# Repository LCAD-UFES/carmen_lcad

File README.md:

# carmen_lcad

Version of the Carmen Robot Navigation Toolkit developed by LCAD for IARA - the Intelligent Autonomous Robotic Autonomobile.

This software is being developed with the support of DI/LCAD/UFES and is financed in part by Fundação de Amparo à Pesquisa do Espírito Santo – Brazil (FAPES), Conselho Nacional de Desenvolvimento Científico e Tecnológico – Brasil (CNPq), and Coordenação de Aperfeiçoamento de Pessoal de Nível Superior – Brasil (CAPES).

## Instalação

### ➡️ Ubuntu 26.04 LTS — [**tutorial completo, aqui no repositório**](doc/migracao_ubuntu26/install/INSTALL_UBUNTU_26.04.md)

Esta é a versão recomendada e o tutorial mais atual. Ele fica **dentro do próprio
repositório** (não na wiki).

Resumo do caminho (o passo a passo com todos os detalhes está no tutorial):

```bash
git clone https://github.com/LCAD-UFES/carmen_lcad.git ~/carmen_lcad
# 1. adicionar o bloco #CARMEN no ~/.bashrc  (CARMEN_HOME, PATH, LD_LIBRARY_PATH)
# 2. instalar os pacotes apt  (build tools, Boost, OpenCV/PCL/g2o, GTK & cia.)
# 3. instalar o GtkGLExt da fonte, se ainda não estiver na máquina
cd $CARMEN_HOME/src
./configure --nojava --nocuda --noqt3       # Enter em todas as perguntas
make -j$(nproc)
```

Junto do tutorial estão os outros documentos da migração para o 26.04 — úteis quando
algo não compila:

| Documento | Para quê |
|---|---|
| [`install/INSTALL_UBUNTU_26.04.md`](doc/migracao_ubuntu26/install/INSTALL_UBUNTU_26.04.md) | **O tutorial de instalação.** Comece por aqui |
| [`install/00_` a `05_`](doc/migracao_ubuntu26/install/) | O detalhe e o porquê de cada passo do tutorial |
| [`CHANGELOG.md`](doc/migracao_ubuntu26/CHANGELOG.md) | Cada alteração de código/Makefile feita na migração, e por quê |
| [`AUDIT_DEPENDENCIAS.md`](doc/migracao_ubuntu26/AUDIT_DEPENDENCIAS.md) | Nome e versão de cada dependência no 26.04: o que mudou de nome, o que sumiu do apt |
| [`install/05_pendencias_conhecidas.md`](doc/migracao_ubuntu26/install/05_pendencias_conhecidas.md) | O que ficou pendente e por quê |

### Versões anteriores (wiki)

Português:

- [Install for Ubuntu 12.04](http://www.lcad.inf.ufes.br/wiki/index.php/Instala%C3%A7%C3%A3o_Carmen_para_Ubuntu_12.04.3)
- [Install for Ubuntu 16.04](https://github.com/LCAD-UFES/carmen_lcad/wiki/Installing-Carmen-LCAD-on-Ubuntu-16.04-(Portuguese))
- [Install for Ubuntu 18.04](https://github.com/LCAD-UFES/carmen_lcad/wiki/Installing-Carmen-LCAD-on-Ubuntu-18.04-(Portuguese))
- [Install for Ubuntu 20.04](https://github.com/LCAD-UFES/carmen_lcad/wiki/Installing-Carmen-on-Ubuntu-20.04-(Portuguese))

English:

- [Install for Ubuntu 12.04](https://github.com/LCAD-UFES/carmen_lcad/wiki/Installing-Carmen-LCAD-on-Ubuntu-12.04.3-(English))
- [Install for Ubuntu 14.04](https://github.com/LCAD-UFES/carmen_lcad/wiki/Installing-Carmen-LCAD-on-Ubuntu-14.04-(English))
- [Install for Ubuntu 16.04](https://github.com/LCAD-UFES/carmen_lcad/wiki/Installing-Carmen-LCAD-on-Ubuntu-16.04-(English))
- [Install for Ubuntu 18.04](https://github.com/LCAD-UFES/carmen_lcad/wiki/Installing-Carmen-LCAD-on-Ubuntu-18.04-(English))
- [Install for Ubuntu 20.04](https://github.com/LCAD-UFES/carmen_lcad/wiki/Installing-Carmen-on-Ubuntu-20.04-(English))

## Rodando

Os `.ini` de parâmetros ficam em `src/`, e os binários rodam a partir de `bin/` — os
caminhos dentro dos `.ini` são relativos a `bin/`.

```bash
cd $CARMEN_HOME/bin
./central
```

```bash
cd $CARMEN_HOME/bin
./proccontrol process-volta_da_ufes_playback_viewer_3D.ini
```

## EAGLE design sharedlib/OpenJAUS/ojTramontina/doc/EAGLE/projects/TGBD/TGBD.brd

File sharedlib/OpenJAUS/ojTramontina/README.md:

# ojEcoTech4
e.coTech4 Driver

Para rodar o sistema de freio ou volante, levante o barramento can (precisa do CANable):

 sudo ip link set can0 up type can bitrate 500000

Depois rode em terminais separados:

 ../ojNodeManager/bin/ojNodeManager ../ojNodeManager/nodeManager_EcoTech4.conf a
 ../ojTorc/bin/ojTorc {tecle w para entrar em Wrench Efforts Mode}
 bin/ojEcoTech4-2 can0 can0

Para compilar o codigo do ESP32:
 cd breaks
 . $HOME/esp/esp-idf/export.sh {o ponto eh importante}
 make
 make flash {para programar o ESP32}
 make monitor {para visualisar a saida do ESP32 via a sua USB}

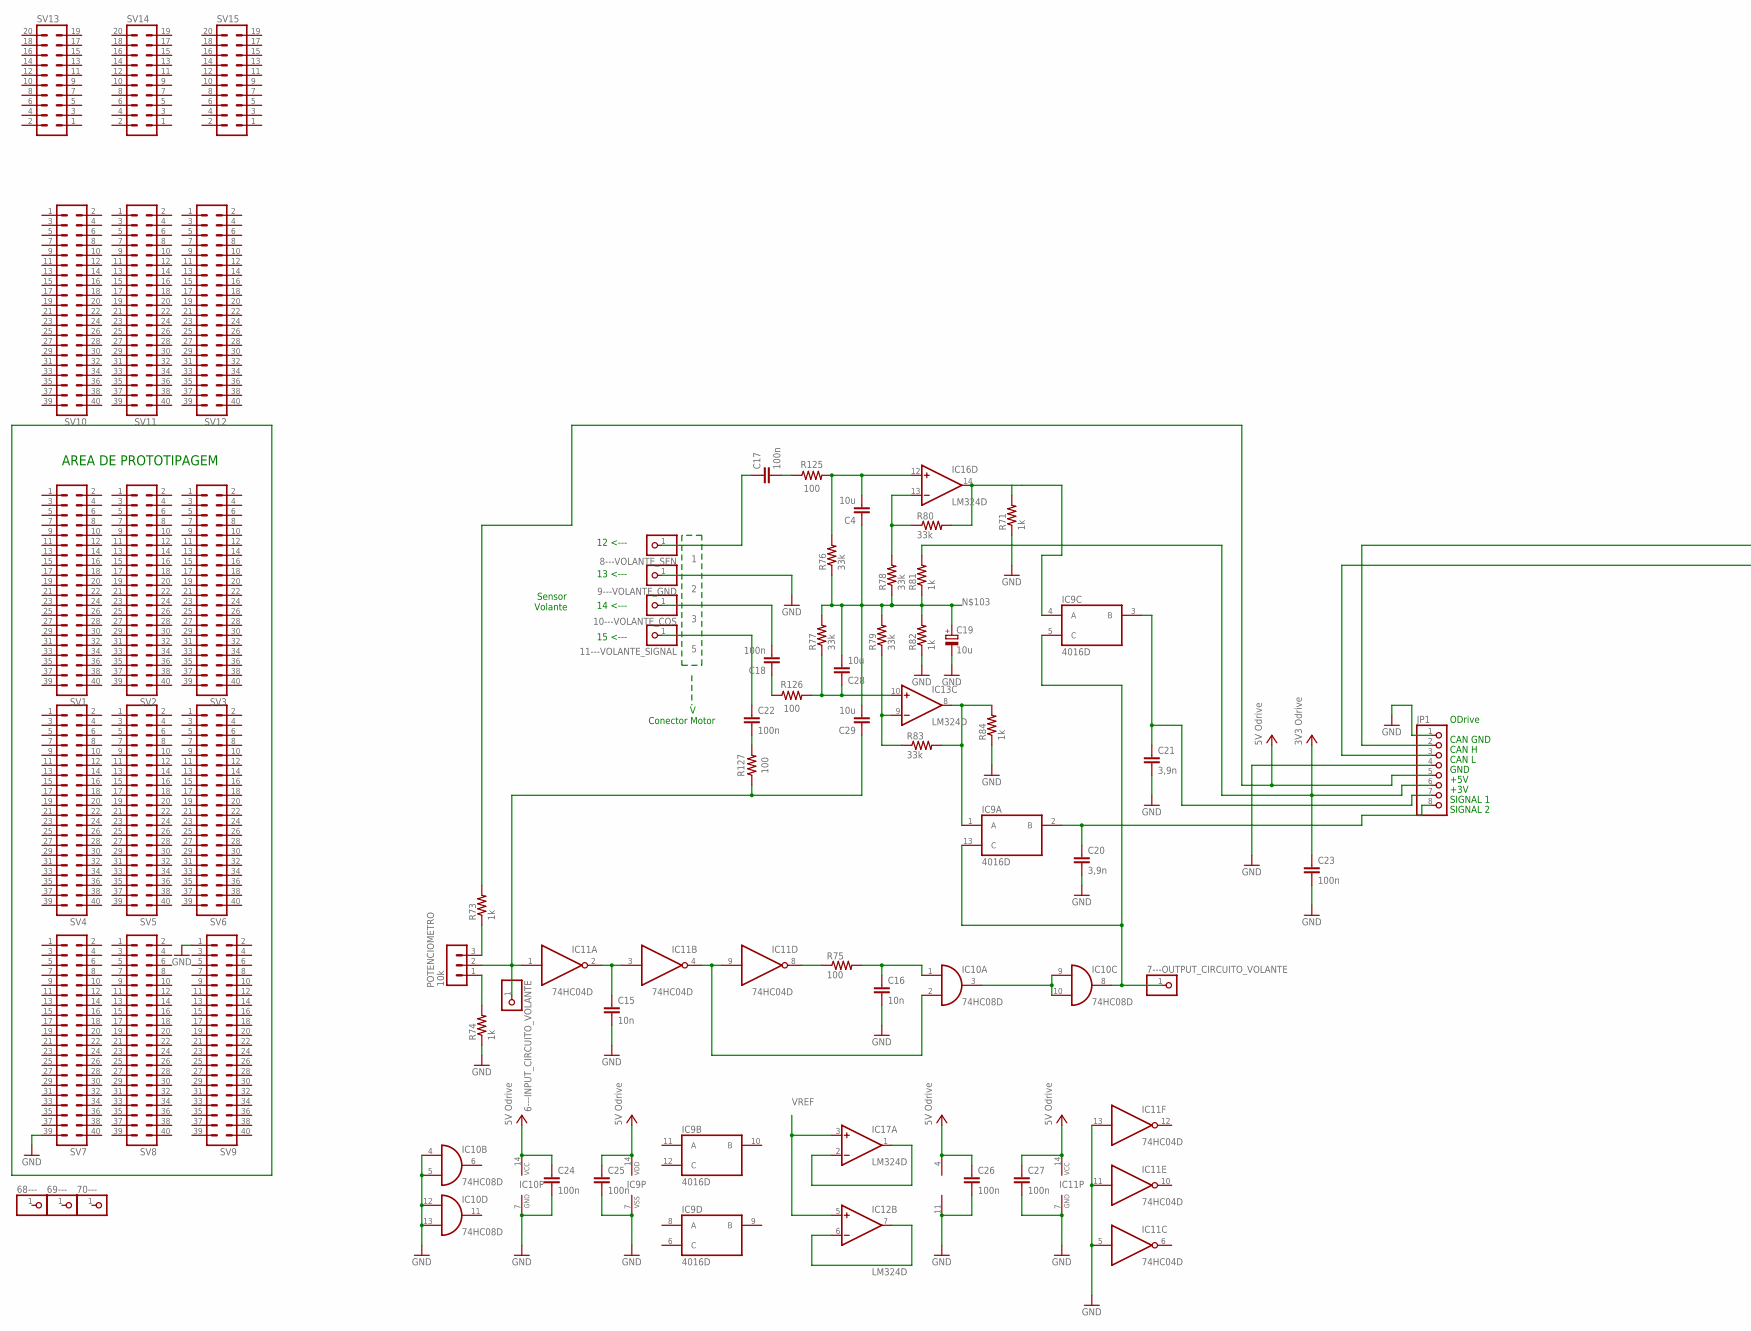
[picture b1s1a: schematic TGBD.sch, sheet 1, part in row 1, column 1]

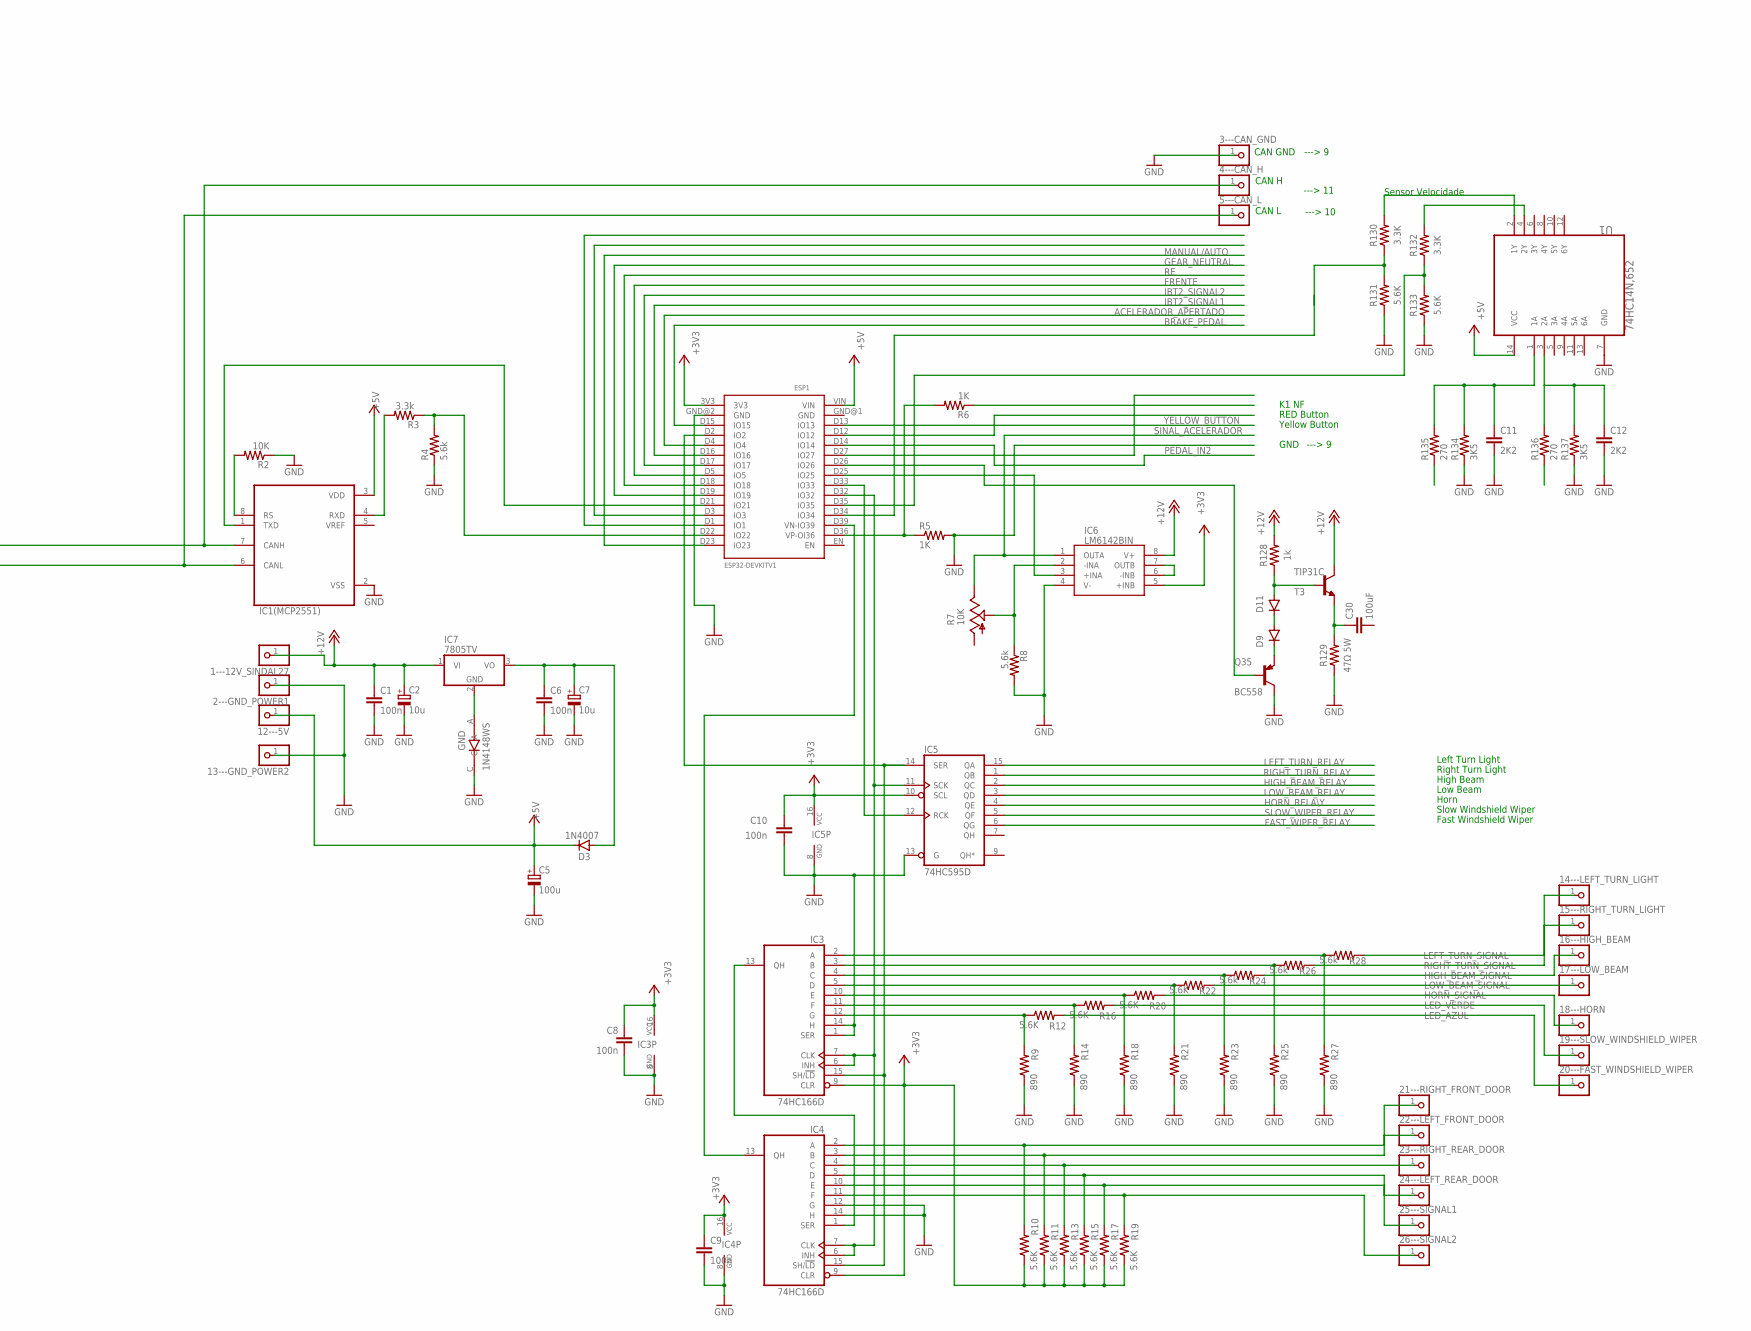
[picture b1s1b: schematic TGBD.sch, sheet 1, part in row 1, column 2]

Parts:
1---12V_SINDAL27, 2---GND_POWER1, 3---CAN_GND, 4---CAN_H, 5---CAN_L, 6---INPUT_CIRCUITO_VOLANTE, 7---OUTPUT_CIRCUITO_VOLANTE, 12---5V, 13---GND_POWER2, 14---LEFT_TURN_LIGHT, 15---RIGHT_TURN_LIGHT, 16---HIGH_BEAM, 17---LOW_BEAM, 18---HORN, 19---SLOW_WINDSHIELD_WIPER, 20---FAST_WINDSHIELD_WIPER, 21---RIGHT_FRONT_DOOR, 22---LEFT_FRONT_DOOR, 23---RIGHT_REAR_DOOR, 24---LEFT_REAR_DOOR, 25---SIGNAL1, 26---SIGNAL2, 68---, 69---, 70---: PINHD-1X1; 1X01
8---VOLANTE_SEN: 1; 1X01
9---VOLANTE_GND: 2; 1X01
10---VOLANTE_COS: 3; 1X01
11---VOLANTE_SIGNAL: 5; 1X01
C1, C6, C8, C9, C10, C17, C18, C22, C23, C24, C25, C26, C27: 100n; C0402
C2, C7, C19: 10u; A/3216-18R
C4, C28, C29: 10u; C0402
C5: 100u; UD-6,3X7,7_NICHICON
C11, C12: 2K2; C2.5-3
C15, C16: 10n; C0402
C20, C21: 3,9n; C0402
C30: 100uF; C2.5-2
D3: 1N4007; SOD123
D9, D11: 1N4148DO35-7; DO35-7
ESP1: ESP32DEVKITV1; ESP32-DEVKITV1
GND: 1N4148WS; SODFL2512X100N
IC1(MCP2551): MCP2551-I/SN; SOIC127P599X175-8N
IC3, IC4: 74HC166D; SO16
IC5: 74HC595D; SO16
IC6: LM6142BIN; DIP254P762X508-8
IC7: 7805TV; TO220V
IC8, IC12, IC13, IC16, IC17: LM324D; SO14
IC9: 4016D; SO14
IC10: 74HC08D; SO14
IC11: 74HC04D; SO14
JP1: PINHD-1X8; 1X08
POTENCIOMETRO: 10k; MA03-1
Q35: BC558; TO92260P520H933-3
R2: 10K; R0603
R3: 3.3k; R0402
R4, R8, R24, R26, R28: 5.6k; R0603
R5, R6: 1K; R0402
R7: 10K; CT6
R9, R14, R18, R21, R23, R25, R27: 890; R0603
R10, R11, R12, R13, R15, R16, R17, R19, R20, R22: 5.6K; R0603
R71, R73, R74, R81, R82, R84: 1k; R0402
R75: 100; R0603
R76, R77, R78, R79, R80, R83: 33k; R0402
R125, R126, R127: 100; RESC1005X40
R128: 1k; RESAD724W46L381D178B
R129: 47Ω 5W; RESAD724W46L381D178B
R130, R132: 3.3K; RESAD724W46L381D178B
R131, R133: 5.6K; RESAD724W46L381D178B
R134, R137: 3K5; 0204/7
R135, R136: 270; 0204/7
SV1, SV2, SV3, SV4, SV5, SV6, SV7, SV8, SV9, SV10, SV11, SV12: MA20-2
SV13, SV14, SV15: MA10-2
T3: TIP31C; TO220
U1: 74HC14N,652; DIP254P762X420-14

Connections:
3V3_ODRIVE: C23.1, JP1.6, R81.2
5V_ODRIVE: C24.1, C25.1, C26.1, C27.1, IC8.4 (V+), IC9.14 (VDD), IC10.14 (VCC), IC11.14 (VCC), JP1.5, R73.2
9---GND: 9---VOLANTE_GND.1
+3V3: C8.1, C9.1, C10.1, ESP1.3V3, IC3.9 (CLR), IC3.16 (VCC), IC4.9 (CLR), IC4.16 (VCC), IC5.10 (SCL), IC5.16 (VCC), IC6.5 (+INB), R10.1, R11.1, R13.1, R15.1, R17.1, R19.1
+5V: 12---5V.1, C5.+, D3.C, ESP1.VIN, IC1(MCP2551).3 (VDD), U1.14 (VCC); also elsewhere on the board
+12V: 1---12V_SINDAL27.1, C1.1, C2.+, IC6.8 (V+), IC7.1 (VI), R128.2, T3.2 (C); also elsewhere on the board
ACELERADOR_APERTADO: ESP1.D4 (IO4); also elsewhere on the board
AUTONOMO/NAO: ESP1.D27 (IO27)
BRAKE_PEDAL: ESP1.D15 (IO15)
FAST_WIPER_RELAY: IC5.6 (QG); also elsewhere on the board
FRENTE: ESP1.D5 (IO5); also elsewhere on the board
GEAR_NEUTRAL: ESP1.D19 (IO19)
GND: 2---GND_POWER1.1, 3---CAN_GND.1, 13---GND_POWER2.1, C1.2, C2.-, C5.-, C6.2, C7.-, C8.2, C9.2, C10.2, C11.2, C12.2, C15.2, C16.2, C19.-, C20.2, C21.2, C23.2, C24.2, C25.2, C26.2, C27.2, ESP1.GND@2 (GND), GND.C, IC1(MCP2551).2 (VSS), IC3.1 (SER), IC3.8 (GND), IC3.14 (H), IC4.8 (GND), IC4.12 (G), IC4.14 (H), IC5.8 (GND), IC5.13 (G), IC6.4 (V-), IC8.11 (V-), IC9.7 (VSS), IC10.4 (I0), IC10.5 (I1), IC10.7 (GND), IC10.12 (I0), IC10.13 (I1), IC11.5 (I), IC11.7 (GND), IC11.11 (I), IC11.13 (I), JP1.1, JP1.4, Q35.1 (C), R2.1, R4.1, R5.2, R8.2, R9.1, R14.1, R18.1, R21.1, R23.1, R25.1, R27.1, R71.1, R74.1, R82.1, R84.1, R129.1, R131.1, R133.1, R134.1, R137.1, SV7.39, SV9.1, U1.7 (GND); also elsewhere on the board
HIGH_BEAM_RELAY: IC5.2 (QC); also elsewhere on the board
HIGH_BEAM_SIGNAL: 16---HIGH_BEAM.1, R24.2; also elsewhere on the board
HORN_RELA\Y: IC5.4 (QE)
HORN_SIGNAL: 18---HORN.1, R20.2; also elsewhere on the board
IBT2_SIGNAL1: ESP1.D16 (IO16)
IBT2_SIGNAL2: ESP1.D17 (IO17)
LED_AZUL: 20---FAST_WINDSHIELD_WIPER.1, R12.2; also elsewhere on the board
LED_VERDE: 19---SLOW_WINDSHIELD_WIPER.1, R16.2; also elsewhere on the board
LEFT_TURN_RELAY: IC5.15 (QA); also elsewhere on the board
LEFT_TURN_SIGNAL: 14---LEFT_TURN_LIGHT.1, R28.2; also elsewhere on the board
LOW_BEAM_RELAY: IC5.3 (QD); also elsewhere on the board
LOW_BEAM_SIGNAL: 17---LOW_BEAM.1, R22.2; also elsewhere on the board
MANUAL/AUTO: ESP1.D23 (IO23); also elsewhere on the board
unnamed: IC6.6 (-INB), IC6.7 (OUTB)
unnamed: ESP1.D25 (IO25), IC6.3 (+INA)
unnamed: IC6.2 (-INA), R7.S, R8.1
unnamed: ESP1.D21 (IO21), IC1(MCP2551).1 (TXD)
unnamed: IC1(MCP2551).8 (RS), R2.2
unnamed: IC1(MCP2551).4 (RXD), R3.2
unnamed: 4---CAN_H.1, IC1(MCP2551).7 (CANH), JP1.2
unnamed: GND.A, IC7.2 (GND)
unnamed: ESP1.D32 (IO32), IC3.6 (INH), IC3.7 (CLK), IC4.6 (INH), IC4.7 (CLK), IC5.11 (SCK)
unnamed: ESP1.D22 (IO22), R3.1, R4.2
unnamed: C6.1, C7.+, D3.A, IC7.3 (VO)
unnamed: POTENCIOMETRO.3, R73.1
unnamed: ESP1.D36 (VP-OI36), R5.1, R6.2
unnamed: D9.C, Q35.3 (E)
unnamed: IC3.2 (A), R27.2, R28.1
unnamed: ESP1.D33 (IO33), IC5.12 (RCK)
unnamed: IC3.3 (B), R25.2, R26.1
unnamed: IC3.4 (C), R23.2, R24.1
unnamed: IC3.5 (D), R21.2, R22.1
unnamed: ESP1.D39 (VN-IO39), IC4.13 (QH)
unnamed: 21---RIGHT_FRONT_DOOR.1, IC4.2 (A), R10.2
unnamed: 22---LEFT_FRONT_DOOR.1, IC4.3 (B), R11.2
unnamed: 23---RIGHT_REAR_DOOR.1, IC4.4 (C), R13.2
unnamed: 24---LEFT_REAR_DOOR.1, IC4.5 (D), R15.2
unnamed: IC3.13 (QH), IC4.1 (SER)
unnamed: IC3.10 (E), R18.2, R20.1
unnamed: IC3.11 (F), R14.2, R16.1
unnamed: IC3.12 (G), R9.2, R12.1
unnamed: C15.1, IC11.2 (O), IC11.3 (I)
unnamed: IC10.3 (O), IC10.9 (I0), IC10.10 (I1)
unnamed: 5---CAN_L.1, IC1(MCP2551).6 (CANL), JP1.3
unnamed: POTENCIOMETRO.1, R74.2
unnamed: C4.1, C19.+, C28.2, C29.2, R76.1, R77.2, R78.1, R79.2, R81.1, R82.2
unnamed: IC11.8 (O), R75.1
unnamed: C16.1, IC10.1 (I0), R75.2
unnamed: IC10.2 (I1), IC11.4 (O), IC11.9 (I)
unnamed: C4.2, IC16.12 (+IN), R76.2, R125.2
unnamed: 8---VOLANTE_SEN.1, C17.1
unnamed: C11.1, R134.2, R135.2, U1.1 (1A)
unnamed: IC13.9 (-IN), R79.1, R83.1
unnamed: IC16.13 (-IN), R78.2, R80.1
unnamed: 10---VOLANTE_COS.1, C18.2
unnamed: IC9.1 (A), IC13.8 (OUT), R83.2, R84.2
unnamed: C20.1, IC9.2 (B), JP1.8
unnamed: IC17.1 (OUT), IC17.2 (-IN)
unnamed: IC12.6 (-IN), IC12.7 (OUT)
unnamed: 7---OUTPUT_CIRCUITO_VOLANTE.1, IC9.5 (C), IC9.13 (C), IC10.8 (O)
unnamed: C21.1, IC9.3 (B), JP1.7
unnamed: 11---VOLANTE_SIGNAL.1, C22.1
unnamed: C28.1, IC13.10 (+IN), R77.1, R126.2
unnamed: IC9.4 (A), IC16.14 (OUT), R71.2, R80.2
unnamed: 25---SIGNAL1.1, IC4.10 (E), R17.2
unnamed: 26---SIGNAL2.1, IC4.11 (F), R19.2
unnamed: C17.2, R125.1
unnamed: C18.1, R126.1
unnamed: C22.2, R127.2
unnamed: ESP1.D2 (IO2), IC3.15 (SH/!LD), IC4.15 (SH/!LD), IC5.14 (SER)
unnamed: ESP1.D26 (IO26), Q35.2 (B)
unnamed: D9.A, D11.C
unnamed: D11.A, R128.1, T3.1 (B)
unnamed: R130.1, R131.2
unnamed: R130.2, U1.2 (1Y)
unnamed: C30.1, R129.2, T3.3 (E)
unnamed: C12.1, R136.2, R137.2, U1.3 (2A)
unnamed: R132.2, U1.4 (2Y)
unnamed: ESP1.D35 (IO35), R132.1, R133.2
PEDAL_IN1: ESP1.D34 (IO34)
PEDAL_IN2: ESP1.D14 (IO14)
RE: ESP1.D18 (IO18); also elsewhere on the board
RIGHT_TURN_RELAY: IC5.1 (QB); also elsewhere on the board
RIGHT_TURN_SIGNAL: 15---RIGHT_TURN_LIGHT.1, R26.2; also elsewhere on the board
SINAL_ACELERADOR: IC6.1 (OUTA), R7.E; also elsewhere on the board
SLOW_WIPER_RELAY: IC5.5 (QF); also elsewhere on the board
V+: IC12.4 (V+), IC13.4 (V+), IC16.4 (V+), IC17.4 (V+); also elsewhere on the board
V-: IC12.11 (V-), IC13.11 (V-), IC16.11 (V-), IC17.11 (V-)
VREF: 6---INPUT_CIRCUITO_VOLANTE.1, C29.1, IC11.1 (I), IC12.5 (+IN), IC17.3 (+IN), POTENCIOMETRO.2, R127.1
YELLOW_BUTTON: ESP1.D13 (IO13); also elsewhere on the board

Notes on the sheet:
Left Turn Light
Right Turn Light
High Beam
Low Beam
Horn
Slow Windshield Wiper
Fast Windshield Wiper
CAN H
CAN L
K1 NF
RED Button
Yellow Button
GND
---> 9
---> 11
Sensor Volante
ODrive
12 <--- 13 <--- 14 <--- 15 <---
AREA DE PROTOTIPAGEM
CAN GND
+5V
+3V
SIGNAL 1
SIGNAL 2
V Conector Motor
Sensor Velocidade
---> 10

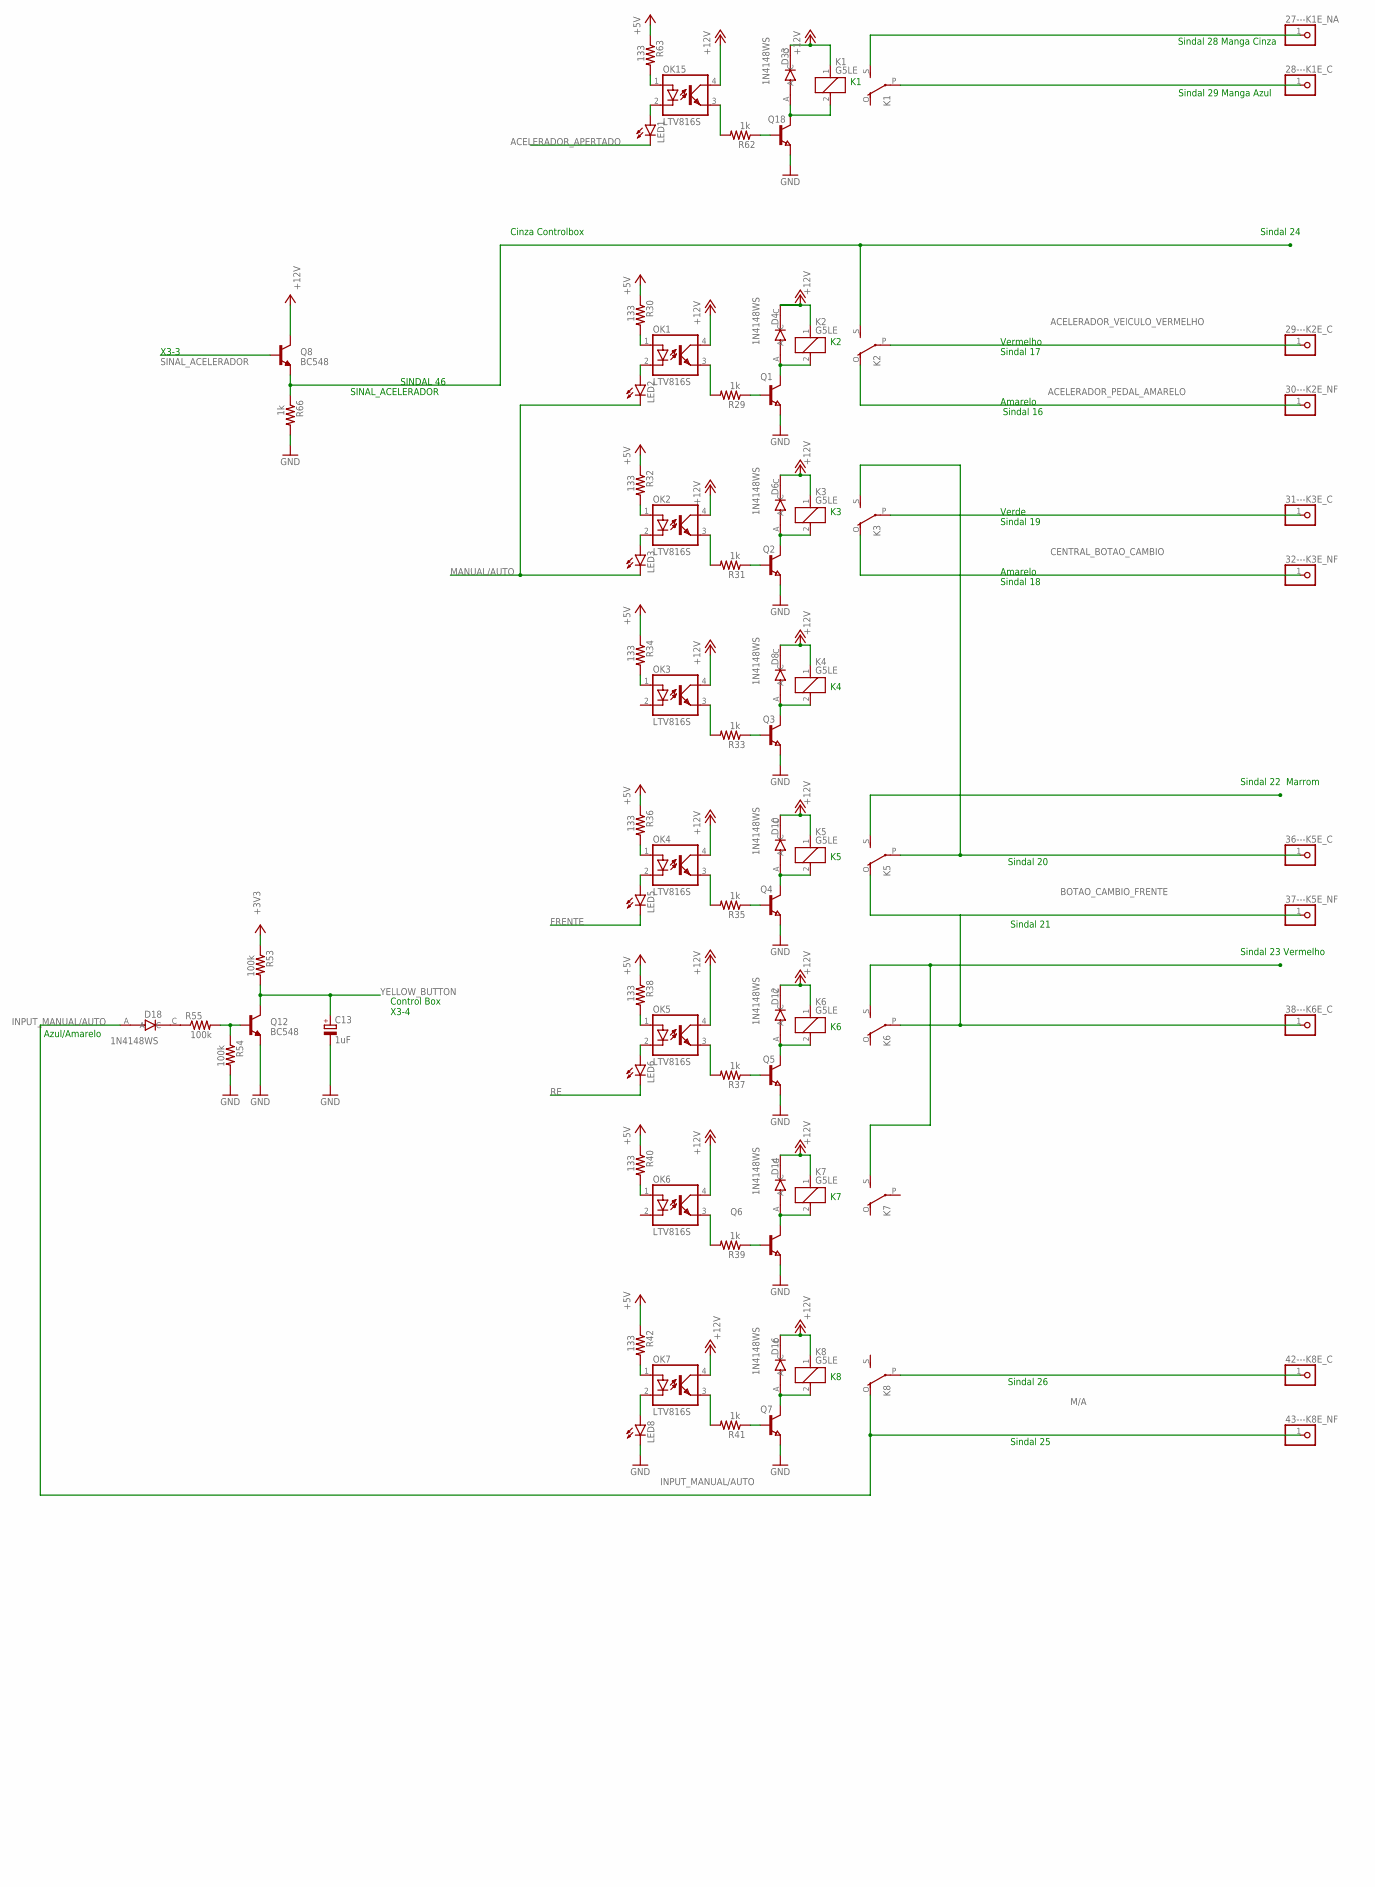
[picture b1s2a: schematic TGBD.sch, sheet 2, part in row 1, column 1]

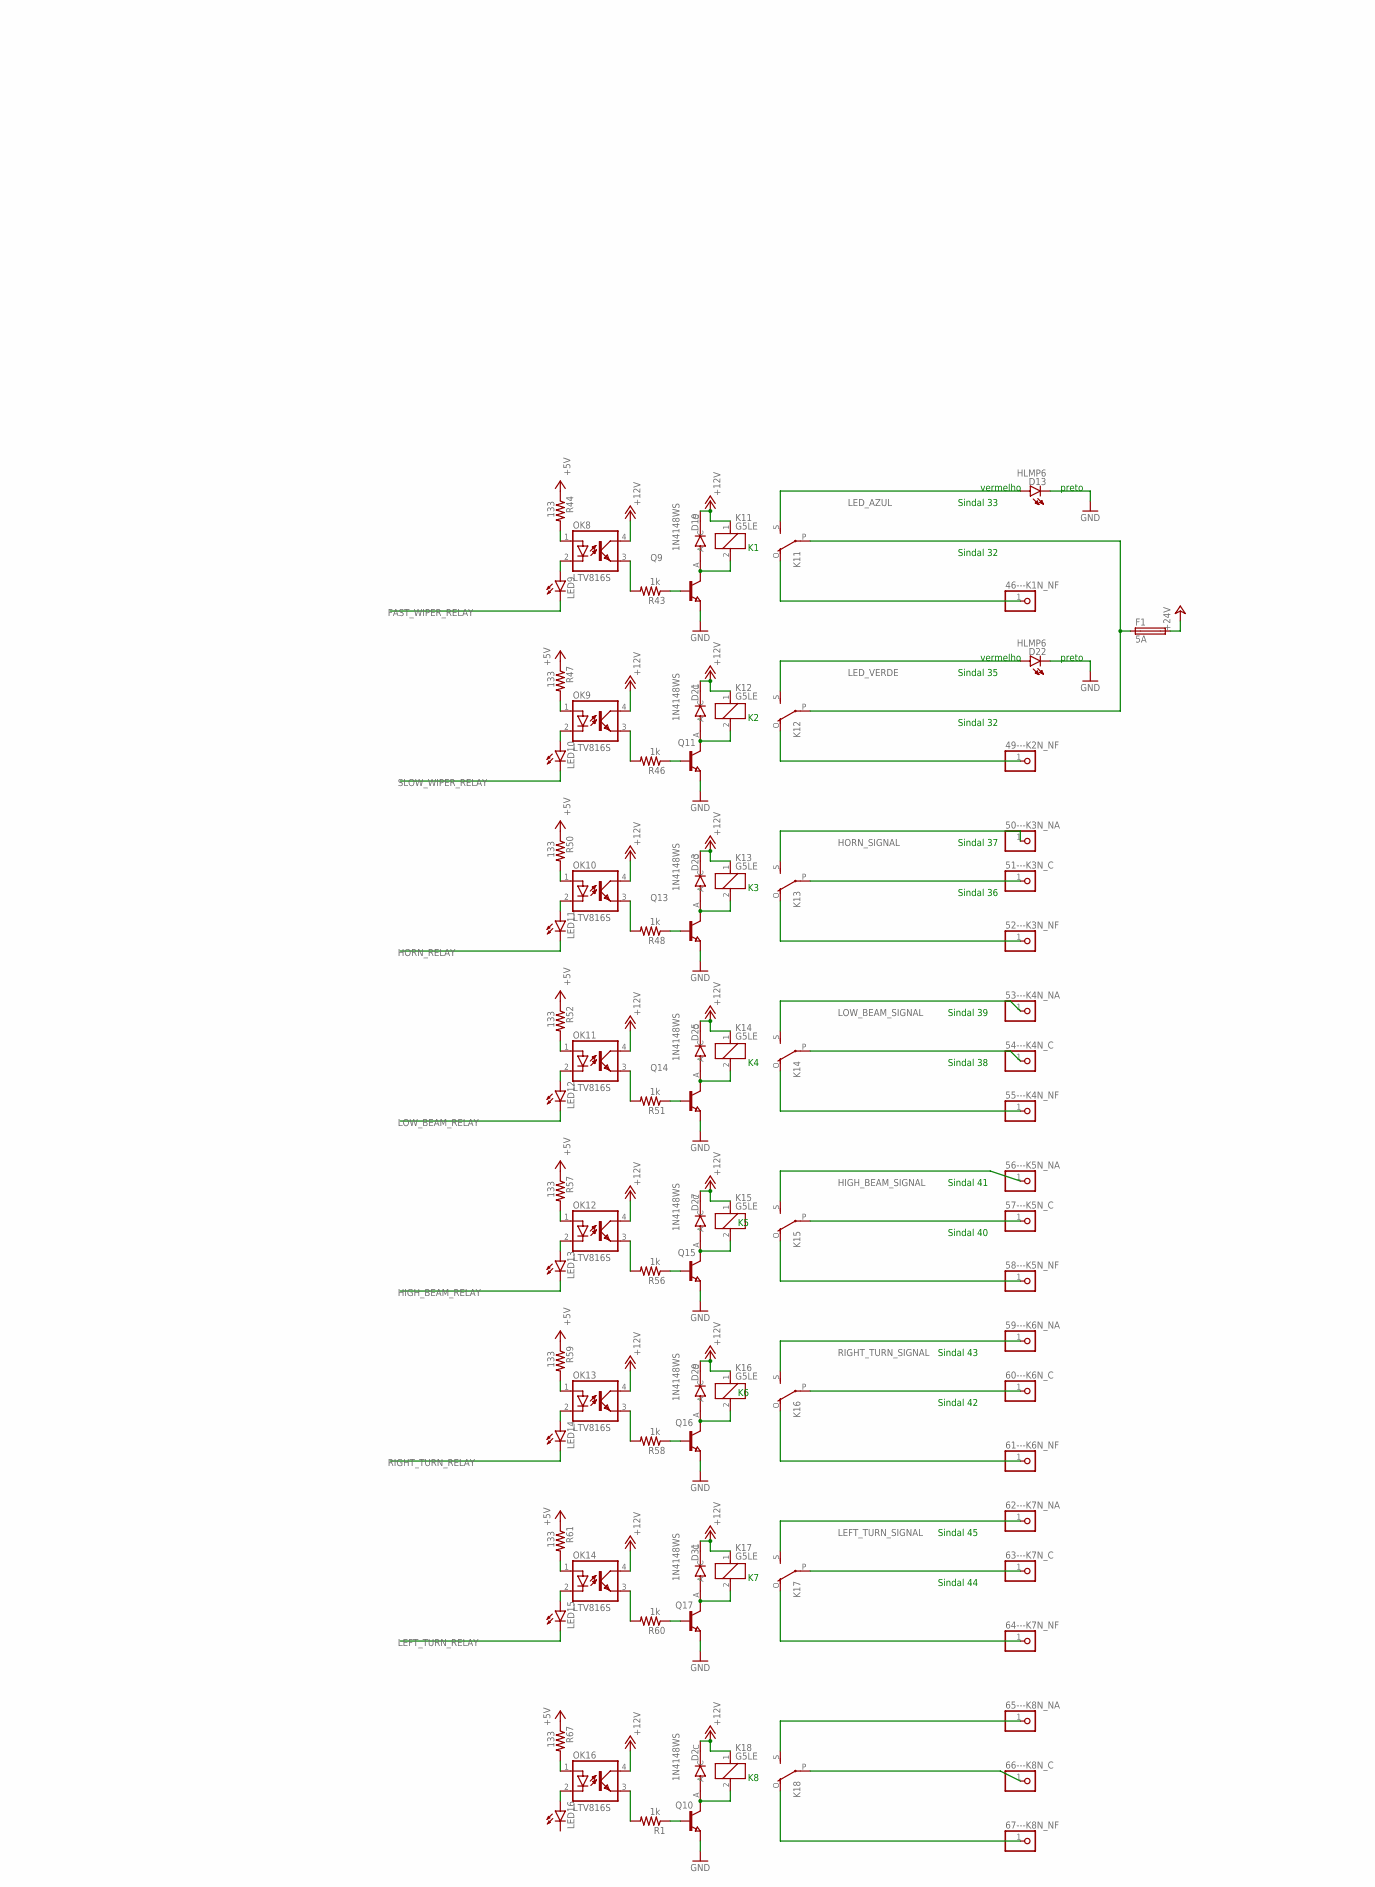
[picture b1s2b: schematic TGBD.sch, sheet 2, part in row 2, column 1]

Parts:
27---K1E_NA, 28---K1E_C, 29---K2E_C, 30---K2E_NF, 31---K3E_C, 32---K3E_NF, 36---K5E_C, 37---K5E_NF, 38---K6E_C, 42---K8E_C, 43---K8E_NF, 46---K1N_NF, 49---K2N_NF, 50---K3N_NA, 51---K3N_C, 52---K3N_NF, 53---K4N_NA, 54---K4N_C, 55---K4N_NF, 56---K5N_NA, 57---K5N_C, 58---K5N_NF, 59---K6N_NA, 60---K6N_C, 61---K6N_NF, 62---K7N_NA, 63---K7N_C, 64---K7N_NF, 65---K8N_NA, 66---K8N_C, 67---K8N_NF: PINHD-1X1; 1X01
C13: 1uF; A/3216-18R
D2, D4, D6, D8, D10, D12, D14, D16, D18, D19, D21, D23, D25, D27, D29, D31, D33: 1N4148WS; SODFL2512X100N
D13, D22: HLMP6
F1: 5A; GSH15
K1, K2, K3, K4, K5, K6, K7, K8, K11, K12, K13, K14, K15, K16, K17, K18: G5LE
LED1, LED2, LED3, LED5, LED6, LED8, LED9, LED10, LED11, LED12, LED13, LED14, LED15, LED16: LEDCHIPLED_0603; CHIPLED_0603
OK1, OK2, OK3, OK4, OK5, OK6, OK7, OK8, OK9, OK10, OK11, OK12, OK13, OK14, OK15, OK16: LTV816S; DIL4-SMD
Q1, Q2, Q3, Q4, Q5, Q6, Q7, Q9, Q10, Q11, Q13, Q14, Q15, Q16, Q17, Q18: NPN-TRANSISTOR_SOT23; SOT23
Q8, Q12: BC548; TO92
R1, R29, R31, R33, R35, R37, R39, R41, R43, R46, R48, R51, R56, R58, R60, R62, R66: 1k; R0402
R30, R32, R34, R36, R38, R40, R42, R44, R47, R50, R52, R57, R59, R61, R63, R67: 133; R0603
R53, R54, R55: 100k; R0402

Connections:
+3V3_ODRIVE: R53.1
+5V: D2.C, D16.C, D19.C, D21.C, D23.C, D25.C, D27.C, D29.C, D31.C, K8.1, K11.1, K12.1, K13.1, K14.1, K15.1, K16.1, K17.1, K18.1, OK7.4 (COL), OK8.4 (COL), OK9.4 (COL), OK10.4 (COL), OK11.4 (COL), OK12.4 (COL), OK13.4 (COL), OK14.4 (COL), OK16.4 (COL), Q8.1 (C), R30.1, R32.1, R34.1, R36.1, R38.1, R40.1, R42.1, R44.1, R47.1, R50.1, R52.1, R57.1, R59.1, R61.1, R63.1, R67.1; also elsewhere on the board
+12V: D4.C, D6.C, D8.C, D10.C, D12.C, D14.C, D33.C, K1.1, K2.1, K3.1, K4.1, K5.1, K6.1, K7.1, OK1.4 (COL), OK2.4 (COL), OK3.4 (COL), OK4.4 (COL), OK5.4 (COL), OK6.4 (COL), OK15.4 (COL); also elsewhere on the board
+24V: F1.2
ACELERADOR_APERTADO: LED1.C; also elsewhere on the board
ACELERADOR_PEDAL_AMARELO: 30---K2E_NF.1, K2.O
ACELERADOR_VEICULO_VERMELHO: 29---K2E_C.1, K2.P
BOTAO_CAMBIO_FRENTE: 37---K5E_NF.1, 38---K6E_C.1, K5.O, K6.P
CENTRAL_BOTAO_CAMBIO: 32---K3E_NF.1, K3.O
COMUM_CAMBIO: 31---K3E_C.1, K3.P, K5.S
FAST_WIPER_RELAY: LED9.C; also elsewhere on the board
FRENTE: LED5.C; also elsewhere on the board
GND: C13.-, D13.K, D22.K, LED8.C, Q1.2 (E), Q2.2 (E), Q3.2 (E), Q4.2 (E), Q5.2 (E), Q6.2 (E), Q7.2 (E), Q9.2 (E), Q10.2 (E), Q11.2 (E), Q12.3 (E), Q13.2 (E), Q14.2 (E), Q15.2 (E), Q16.2 (E), Q17.2 (E), Q18.2 (E), R54.2, R66.2; also elsewhere on the board
HIGH_BEAM_RELAY: LED13.C; also elsewhere on the board
HIGH_BEAM_SIGNAL: 56---K5N_NA.1, K15.S; also elsewhere on the board
HORN_RELAY: LED11.C
HORN_SIGNAL: 50---K3N_NA.1, K13.S; also elsewhere on the board
INPUT_MANUAL/AUTO: 43---K8E_NF.1, D18.A, K8.O
LED_AZUL: D13.A, K11.S; also elsewhere on the board
LED_VERDE: D22.A, K12.S; also elsewhere on the board
LEFT_TURN_RELAY: LED15.C; also elsewhere on the board
LEFT_TURN_SIGNAL: 62---K7N_NA.1, K17.S; also elsewhere on the board
LOW_BEAM_RELAY: LED12.C; also elsewhere on the board
LOW_BEAM_SIGNAL: 53---K4N_NA.1, K14.S; also elsewhere on the board
M/A: 42---K8E_C.1, K8.P
MANUAL/AUTO: LED2.C, LED3.C; also elsewhere on the board
unnamed: 36---K5E_C.1, K5.P
unnamed: K2.S, Q8.3 (E), R66.1
unnamed: OK8.1 (A), R44.2
unnamed: D4.A, K2.2, Q1.3 (C)
unnamed: D18.C, R55.1
unnamed: 65---K8N_NA.1, K18.S
unnamed: K6.S, K7.S
unnamed: LED9.A, OK8.2 (C)
unnamed: OK8.3 (EMIT), R43.2
unnamed: Q9.1 (B), R43.1
unnamed: D16.A, K8.2, Q7.3 (C)
unnamed: OK15.1 (A), R63.2
unnamed: F1.1, K11.P, K12.P
unnamed: LED1.A, OK15.2 (C)
unnamed: OK15.3 (EMIT), R62.2
unnamed: 51---K3N_C.1, K13.P
unnamed: Q18.1 (B), R62.1
unnamed: 54---K4N_C.1, K14.P
unnamed: D33.A, K1.2, Q18.3 (C)
unnamed: 57---K5N_C.1, K15.P
unnamed: 27---K1E_NA.1, K1.S
unnamed: 60---K6N_C.1, K16.P
unnamed: D19.A, K11.2, Q9.3 (C)
unnamed: 63---K7N_C.1, K17.P
unnamed: OK9.1 (A), R47.2
unnamed: OK1.1 (A), R30.2
unnamed: LED10.A, OK9.2 (C)
unnamed: OK9.3 (EMIT), R46.2
unnamed: LED2.A, OK1.2 (C)
unnamed: OK1.3 (EMIT), R29.2
unnamed: Q11.1 (B), R46.1
unnamed: D23.A, K13.2, Q13.3 (C)
unnamed: OK10.1 (A), R50.2
unnamed: LED11.A, OK10.2 (C)
unnamed: Q1.1 (B), R29.1
unnamed: OK10.3 (EMIT), R48.2
unnamed: Q13.1 (B), R48.1
unnamed: D25.A, K14.2, Q14.3 (C)
unnamed: OK11.1 (A), R52.2
unnamed: LED12.A, OK11.2 (C)
unnamed: OK11.3 (EMIT), R51.2
unnamed: Q14.1 (B), R51.1
unnamed: D29.A, K16.2, Q16.3 (C)
unnamed: OK12.1 (A), R57.2
unnamed: LED13.A, OK12.2 (C)
unnamed: OK12.3 (EMIT), R56.2
unnamed: Q15.1 (B), R56.1
unnamed: D27.A, K15.2, Q15.3 (C)
unnamed: OK13.1 (A), R59.2
unnamed: LED14.A, OK13.2 (C)
unnamed: OK13.3 (EMIT), R58.2
unnamed: Q16.1 (B), R58.1
unnamed: D21.A, K12.2, Q11.3 (C)
unnamed: OK14.1 (A), R61.2
unnamed: LED15.A, OK14.2 (C)
unnamed: OK14.3 (EMIT), R60.2
unnamed: Q17.1 (B), R60.1
unnamed: D31.A, K17.2, Q17.3 (C)
unnamed: D6.A, K3.2, Q2.3 (C)
unnamed: D8.A, K4.2, Q3.3 (C)
unnamed: D10.A, K5.2, Q4.3 (C)
unnamed: D12.A, K6.2, Q5.3 (C)
unnamed: D14.A, K7.2, Q6.3 (C)
unnamed: OK16.1 (A), R67.2
unnamed: LED16.A, OK16.2 (C)
unnamed: OK16.3 (EMIT), R1.2
unnamed: Q10.1 (B), R1.1
unnamed: D2.A, K18.2, Q10.3 (C)
unnamed: 67---K8N_NF.1, K18.O
unnamed: 64---K7N_NF.1, K17.O
unnamed: 61---K6N_NF.1, K16.O
unnamed: 58---K5N_NF.1, K15.O
unnamed: 55---K4N_NF.1, K14.O
unnamed: 52---K3N_NF.1, K13.O
unnamed: 49---K2N_NF.1, K12.O
unnamed: 66---K8N_C.1, K18.P
unnamed: 46---K1N_NF.1, K11.O
unnamed: OK2.1 (A), R32.2
unnamed: LED3.A, OK2.2 (C)
unnamed: OK2.3 (EMIT), R31.2
unnamed: Q2.1 (B), R31.1
unnamed: OK3.1 (A), R34.2
unnamed: OK3.3 (EMIT), R33.2
unnamed: Q3.1 (B), R33.1
unnamed: OK4.1 (A), R36.2
unnamed: LED5.A, OK4.2 (C)
unnamed: OK4.3 (EMIT), R35.2
unnamed: Q4.1 (B), R35.1
unnamed: OK5.1 (A), R38.2
unnamed: LED6.A, OK5.2 (C)
unnamed: OK5.3 (EMIT), R37.2
unnamed: Q5.1 (B), R37.1
unnamed: OK6.1 (A), R40.2
unnamed: OK6.3 (EMIT), R39.2
unnamed: Q6.1 (B), R39.1
unnamed: OK7.1 (A), R42.2
unnamed: LED8.A, OK7.2 (C)
unnamed: OK7.3 (EMIT), R41.2
unnamed: Q7.1 (B), R41.1
unnamed: Q12.2 (B), R54.1, R55.2
PEDAL1: 28---K1E_C.1, K1.P
RE: LED6.C; also elsewhere on the board
RIGHT_TURN_RELAY: LED14.C; also elsewhere on the board
RIGHT_TURN_SIGNAL: 59---K6N_NA.1, K16.S; also elsewhere on the board
SINAL_ACELERADOR: Q8.2 (B); also elsewhere on the board
SLOW_WIPER_RELAY: LED10.C; also elsewhere on the board
YELLOW_BUTTON: C13.+, Q12.1 (C), R53.2; also elsewhere on the board

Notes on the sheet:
Amarelo
Verde
Control Box X3-4
Azul/Amarelo
Sindal 16
Sindal 17
Sindal 18
Sindal 19
Sindal 21
Sindal 25
Sindal 26
Sindal 20
Sindal 33
Sindal 32
Sindal 35
Sindal 37
Sindal 36
Sindal 39
Sindal 38
Sindal 41
Sindal 40
Sindal 43
Sindal 42
Sindal 45
Sindal 44
Sindal 29 Manga Azul
Sindal 28 Manga Cinza
SINAL_ACELERADOR
X3-3
SINDAL 46
Sindal 24
Cinza Controlbox
Sindal 22 Marrom
Sindal 23 Vermelho
Vermelho
vermelho
preto
